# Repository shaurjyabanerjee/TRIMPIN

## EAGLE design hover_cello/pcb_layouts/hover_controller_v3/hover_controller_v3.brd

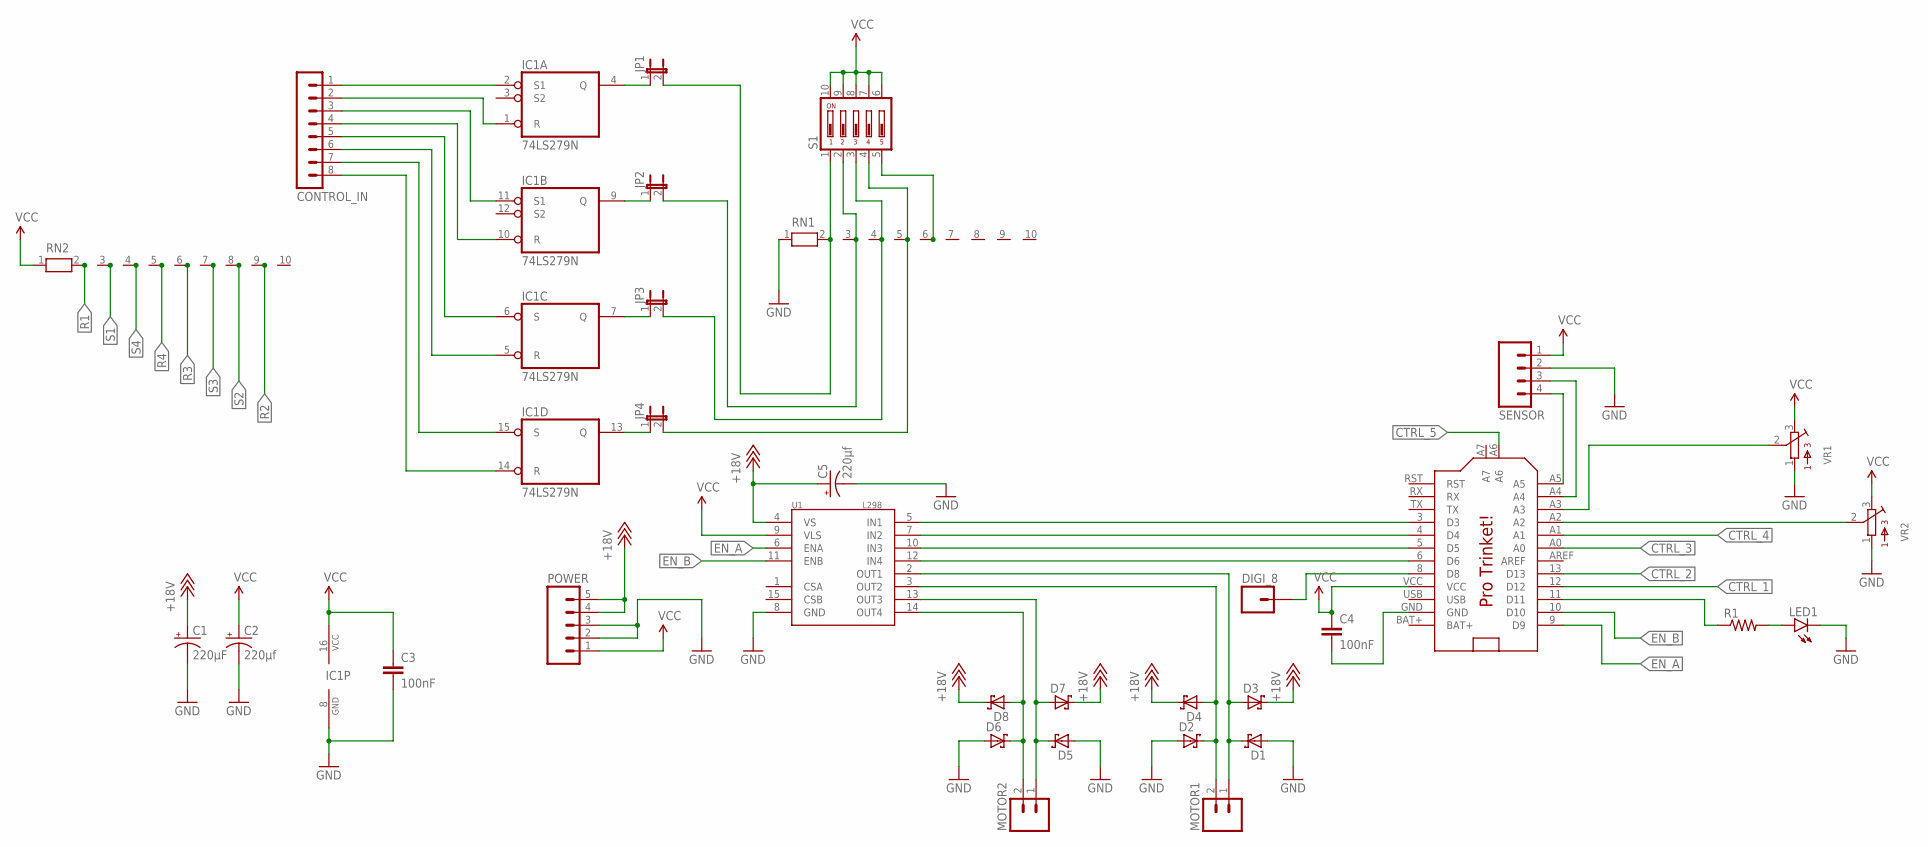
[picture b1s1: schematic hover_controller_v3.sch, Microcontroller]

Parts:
C1: 220µF; CPOL-RADIAL-10UF-25V
C2, C5: 220µf; CPOL-RADIAL-10UF-25V
C3, C4: 100nF; CAP-PTH-5MM
CONTROL_IN: MA08-1
D1, D2, D3, D4, D5, D6, D7, D8: SCHOTTKY-DIODEDO35-7; DO35-7
DIGI_8: M01PTH; 1X01
IC1: 74LS279N; DIL16
JP1, JP2, JP3, JP4: JUMPER-2PTH; 1X02
LED1: LED-3MM-NO_SILK; LED3MM-NS
MOTOR1, MOTOR2: M02PTH; 1X02
POWER: M05JST-VERT; JST-5-PTH-VERT
R1: RESISTORPTH-1/4W; AXIAL-0.4
RN1, RN2: RN09; RN-10
S1: DIP05YL
SENSOR: M04PTH; 1X04
U1: L298; MULTIWATT15
U$1: PRO_TRINKET; PROTRINKET
VR1, VR2: BOURNS_3362P_TRIMMERP; BOURNS_3362P_TRIMMER

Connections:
+18V: C1.1 (+), C5.1 (+), D3.C, D4.C, D7.C, D8.C, POWER.4, POWER.5, U1.4 (VS)
BAT+: U$1.BAT+
CTRL_1: JP1.2, RN1.2, S1.1, U$1.12 (D12)
CTRL_2: JP2.2, RN1.3, S1.2, U$1.13 (D13)
CTRL_3: JP3.2, RN1.4, S1.3, U$1.A0
CTRL_4: JP4.2, RN1.5, S1.4, U$1.A1
CTRL_5: RN1.6, S1.5, U$1.A6
EN_A: U1.6 (ENA), U$1.9 (D9)
EN_B: U1.11 (ENB), U$1.10 (D10)
GND: C1.2 (-), C2.2 (-), C3.2, C5.2 (-), D1.A, D2.A, D5.A, D6.A, IC1.8 (GND), LED1.K (C), POWER.2, POWER.3, RN1.1, SENSOR.2, U1.8 (GND), VR1.1, VR2.1
unnamed: IC1.4 (Q), JP1.1
unnamed: IC1.9 (Q), JP2.1
unnamed: IC1.7 (Q), JP3.1
unnamed: IC1.13 (Q), JP4.1
unnamed: U$1.A2, VR2.2
unnamed: LED1.A, R1.P$2 (2)
unnamed: R1.P$1 (1), U$1.11 (D11)
unnamed: DIGI_8.1, U$1.8 (D8)
unnamed: U$1.A3, VR1.2
unnamed: SENSOR.4, U$1.A5
unnamed: SENSOR.3, U$1.A4
unnamed: U1.5 (IN1), U$1.3 (D3)
unnamed: U1.7 (IN2), U$1.4 (D4)
unnamed: U1.10 (IN3), U$1.5 (D5)
unnamed: U1.12 (IN4), U$1.6 (D6)
unnamed: D1.C, D3.A, MOTOR1.1, U1.2 (OUT1)
unnamed: D2.C, D4.A, MOTOR1.2, U1.3 (OUT2)
unnamed: D5.C, D7.A, MOTOR2.1, U1.13 (OUT3)
unnamed: D6.C, D8.A, MOTOR2.2, U1.14 (OUT4)
unnamed: C4.2, U$1.GND
R1: CONTROL_IN.2, IC1.1 (R), RN2.2
R2: CONTROL_IN.4, IC1.10 (R), RN2.9
R3: CONTROL_IN.6, IC1.5 (R), RN2.6
R4: CONTROL_IN.8, IC1.14 (R), RN2.5
S1: CONTROL_IN.1, IC1.2 (S1), RN2.3
S2: CONTROL_IN.3, IC1.11 (S1), RN2.8
S3: CONTROL_IN.5, IC1.6 (S), RN2.7
S4: CONTROL_IN.7, IC1.15 (S), RN2.4
USB: U$1.USB
VCC: C2.1 (+), C3.1, C4.1, IC1.16 (VCC), POWER.1, RN2.1, S1.6, S1.7, S1.8, S1.9, S1.10, SENSOR.1, U1.9 (VLS), U$1.VCC, VR1.3, VR2.3

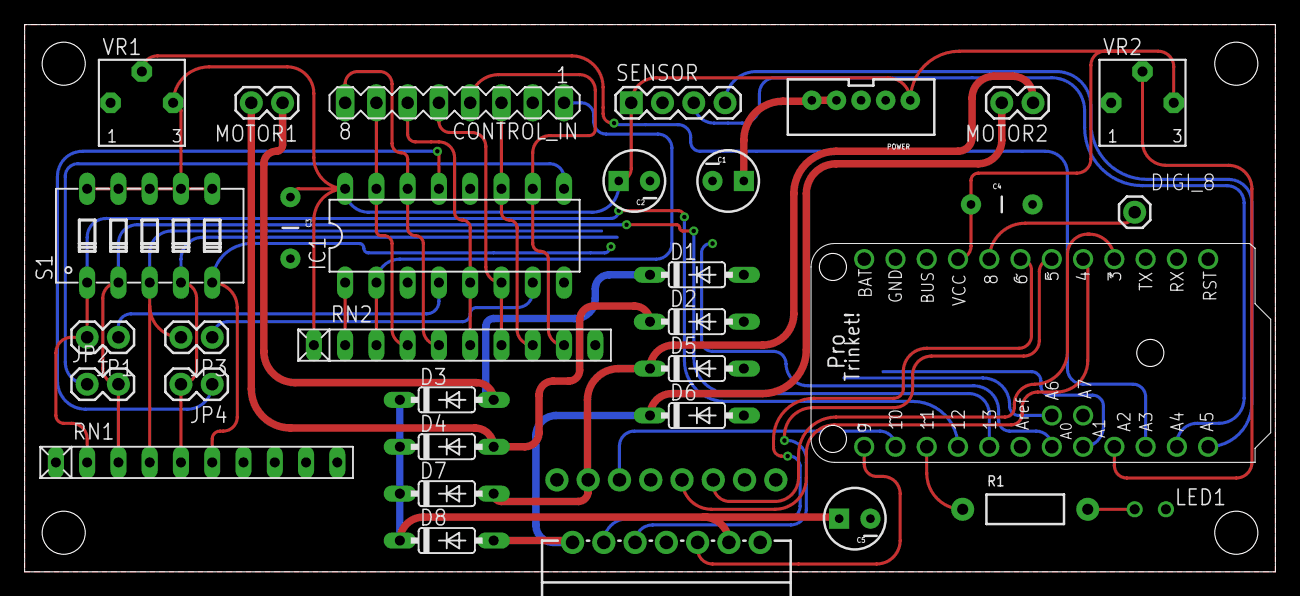
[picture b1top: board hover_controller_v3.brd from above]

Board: 2 copper layers, 101.6 x 44.5 mm, 33 parts (0 on the bottom side), 38 nets.

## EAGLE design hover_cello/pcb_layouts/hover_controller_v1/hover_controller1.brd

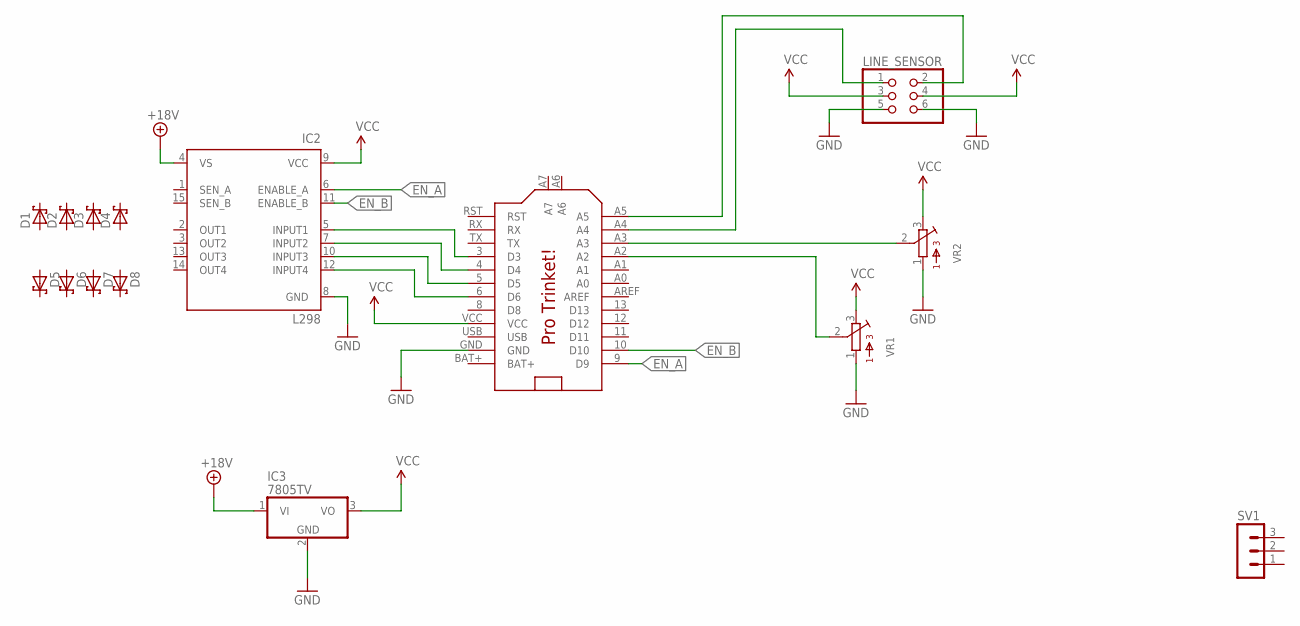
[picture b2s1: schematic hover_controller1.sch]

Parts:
D1, D2, D3, D4, D5, D6, D7, D8: SCHOTTKY-DIODEDO35-7; DO35-7
IC2: L298; MULTIWATT-15
IC3: 7805TV; TO220V
LINE_SENSOR: PINHD-2X3; 2X03
SV1: MA03-1
U$1: PRO_TRINKET; PROTRINKET
VR1, VR2: BOURNS_3362P_TRIMMERP; BOURNS_3362P_TRIMMER

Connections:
+18V: IC2.4 (VS), IC3.1 (VI)
BAT+: U$1.BAT+
EN_A: IC2.6 (ENABLE_A), U$1.9 (D9)
EN_B: IC2.11 (ENABLE_B), U$1.10 (D10)
GND: IC2.8 (GND), IC3.2 (GND), LINE_SENSOR.5, LINE_SENSOR.6, U$1.GND, VR1.1, VR2.1
unnamed: IC2.5 (INPUT1), U$1.3 (D3)
unnamed: IC2.7 (INPUT2), U$1.4 (D4)
unnamed: IC2.10 (INPUT3), U$1.5 (D5)
unnamed: IC2.12 (INPUT4), U$1.6 (D6)
unnamed: U$1.A3, VR2.2
unnamed: U$1.A2, VR1.2
SCL: LINE_SENSOR.2, U$1.A5
SDA: LINE_SENSOR.1, U$1.A4
USB: U$1.USB
VCC: IC2.9 (VCC), IC3.3 (VO), LINE_SENSOR.3, LINE_SENSOR.4, U$1.VCC, VR1.3, VR2.3

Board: 2 copper layers, 15 parts (0 on the bottom side), 13 nets, no tracks yet.

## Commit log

2017-08-14 added motor logic to bitwise line follower sketch
2017-08-15 created Eagle files for hoverboard controller
2017-08-15 fixed some edge case logic weirdness
2017-08-16 fixed annoying line not found bug, added delay on startup
2017-08-18 added L298 DC motor driver to Eagle schematic
2017-08-18 wrote and tested line follower using L298
2017-08-18 figured out and tested individual PWM speed offsets per motor
2017-08-19 added varispeed performance markers
2017-08-20 wrote untested version of simple balance driver
2017-08-20 new untested firmware for motor speed trimmers
2017-08-21 started writing D6T data parser
2017-08-21 increased PWM frequency to 31372.55 Hz for silent motor operation
2017-08-21 wrote and tested zero degree turn firmware with speed limiting
2017-08-21 added speed override button
2017-08-22 added line color invert switch
2017-08-22 added line crossing behaviour. Still untested
2017-08-24 adapted and tested first version of trinket firmware
2017-08-27 wrote basic thermal data visualizer in processing for D6T
2017-09-01 wrote visualizer for AMG 88 thermal sensor
2017-09-01 wrote untested version of spinner firmware
2017-09-01 tested dumb spinner firmware, about to write smart spinner
2017-09-03 added and tested start/stop behaviour
2017-09-04 added vorsetzer folder for firmware
2017-09-04 started new Eagle file for v2 controller
2017-09-04 placed all parts in .brd, started preliminary routing
2017-09-05 wrote and tested V1.0 firmware for hover cello
2017-09-05 reversed correction direction for new sensor configuration
2017-09-20 made new version of board, moved controls
2017-09-26 almost finished routing PCB

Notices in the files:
parts and their libraries:
SparkFun-Aesthetics: Licensing: Creative Commons ShareAlike 4.0 International - https://creativecommons.org/licenses/by-sa/4.0
